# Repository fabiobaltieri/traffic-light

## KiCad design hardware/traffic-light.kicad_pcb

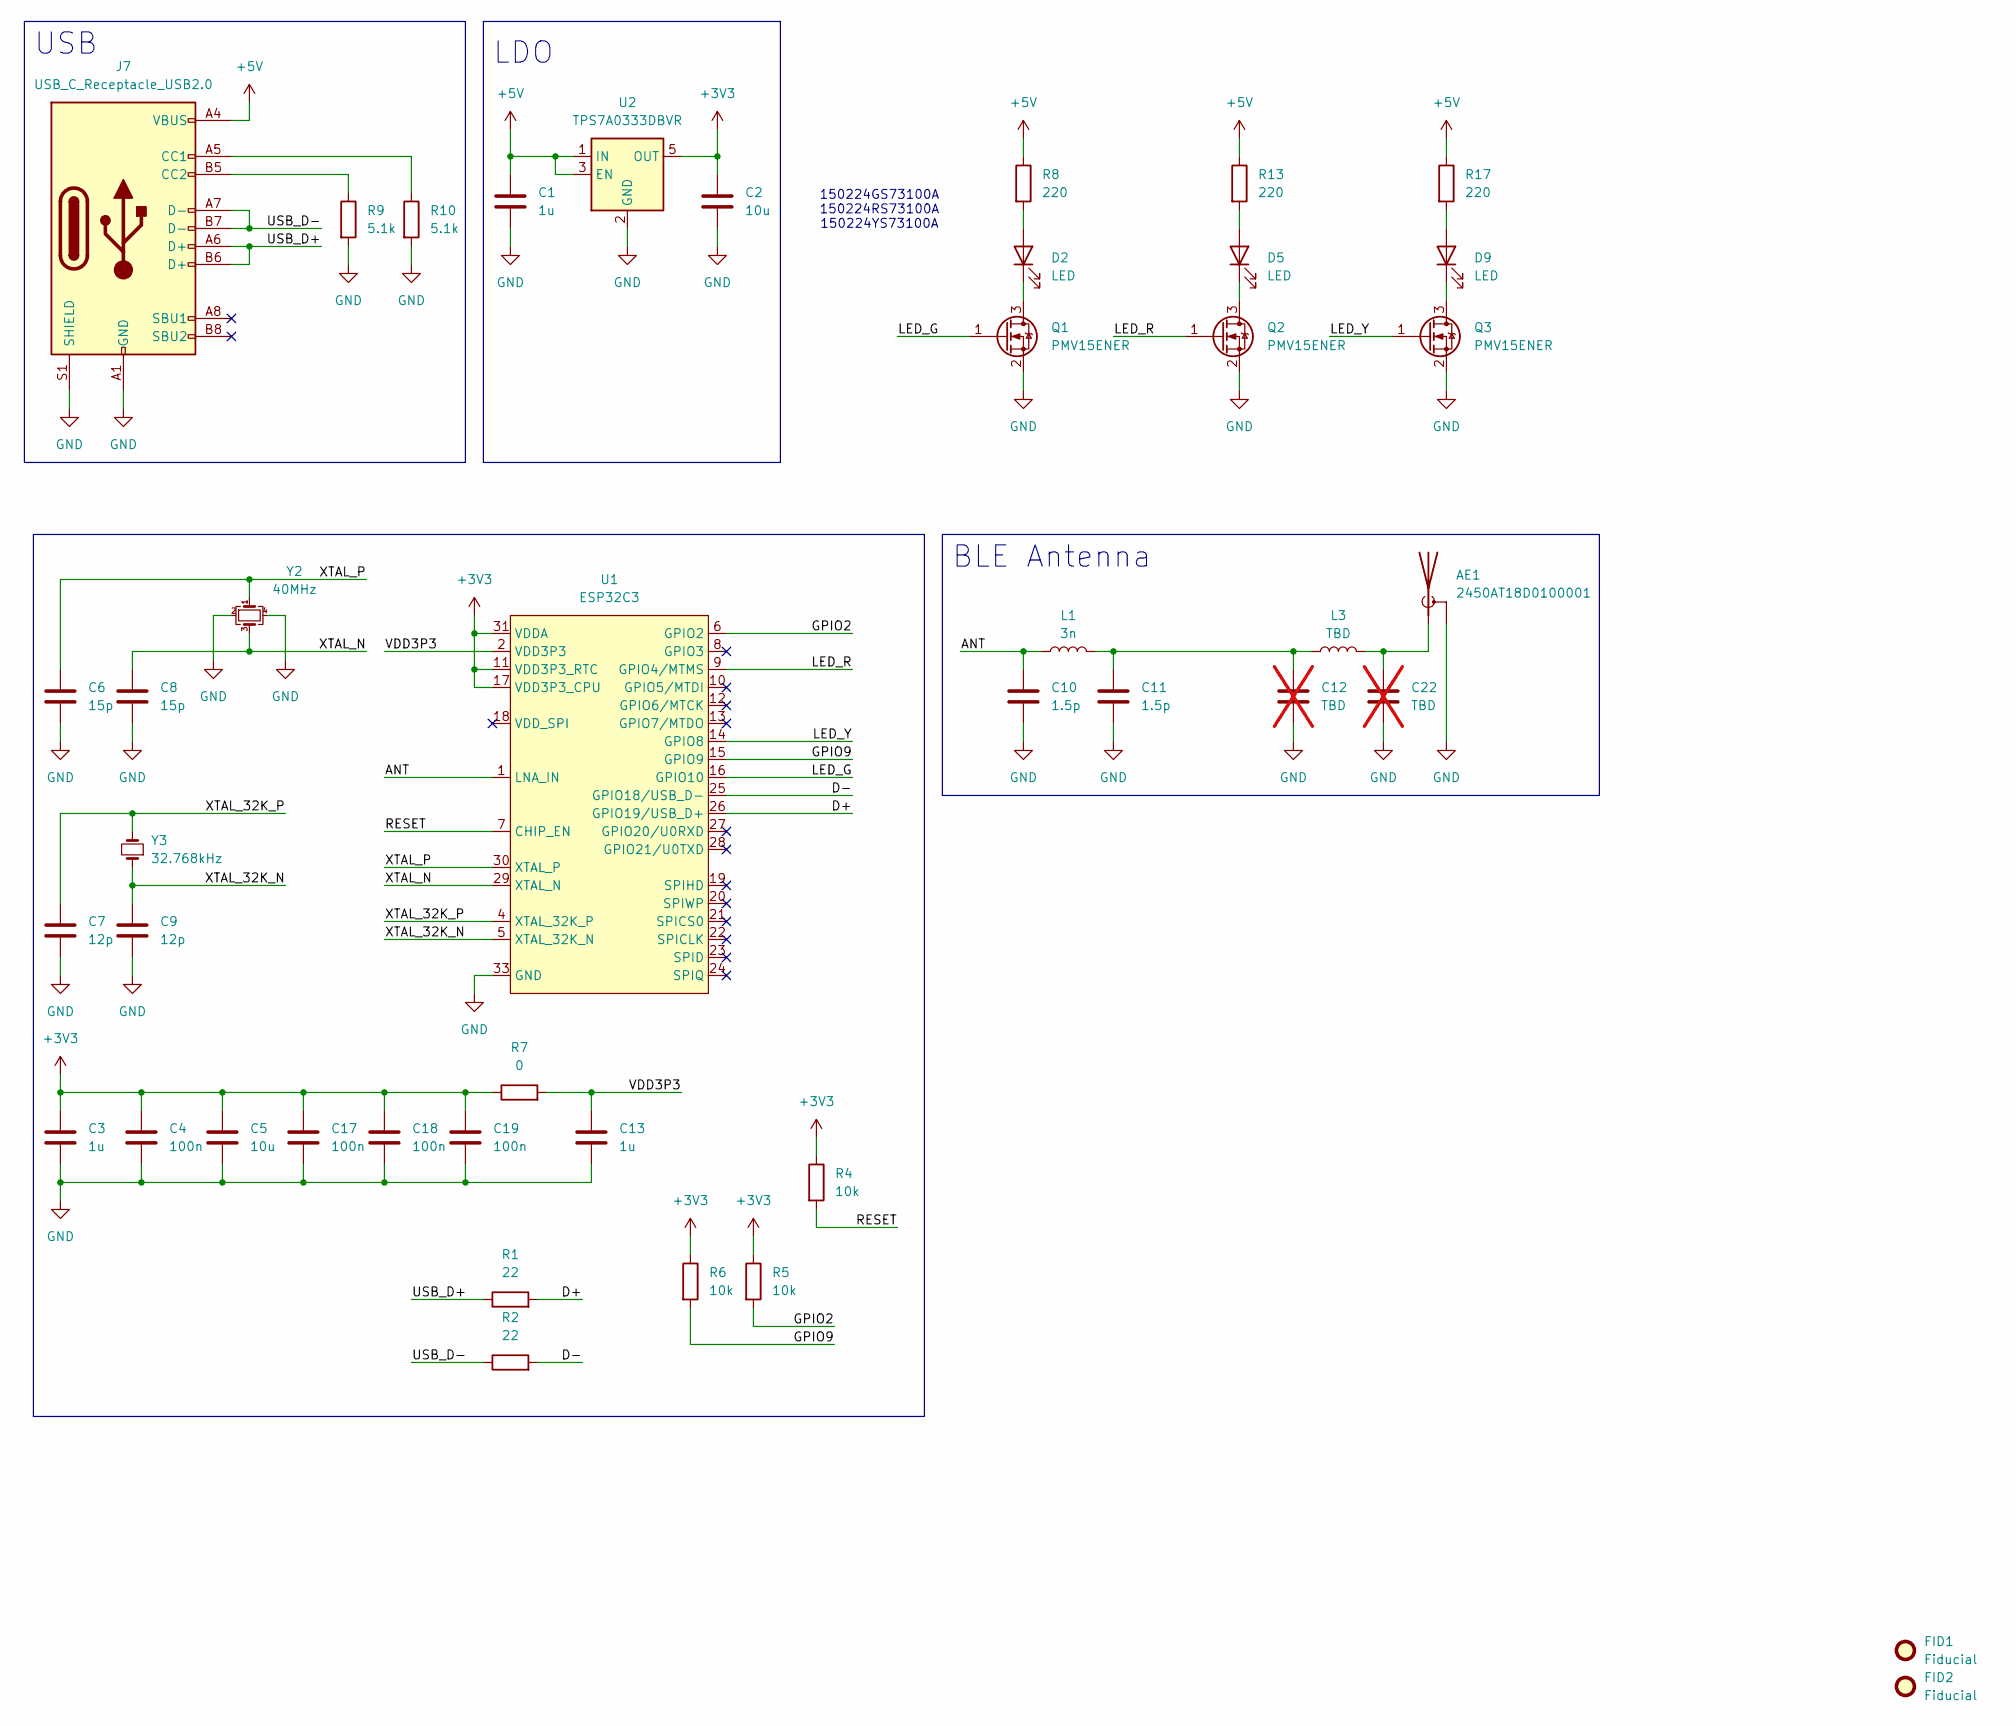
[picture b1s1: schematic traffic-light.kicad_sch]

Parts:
AE1: 2450AT18D0100001; 2450AT18D0100001-R
C1, C3, C13: 1u; C_0402_Worthington
C2, C5: 10u; C_0402_Worthington
C4, C17, C18, C19: 100n; C_0402_Worthington
C6, C8: 15p; C_0402_Worthington
C7, C9: 12p; C_0402_Worthington
C10, C11: 1.5p; C_0402_Worthington
C12, C22: TBD; C_0402_Worthington; not fitted
D2, D5, D9: LED; Wurth_LED_2214
FID1, FID2: Fiducial; Fiducial_0.75mm_Mask1.5mm
J7: USB_C_Receptacle_USB2.0; USB_C_Receptacle_JAE_DX07S016JA1R1500
L1: 3n; L_0402_Worthington
L3: TBD; L_0402_Worthington
Q1, Q2, Q3: PMV15ENER; SOT-23
R1, R2: 22; R_0603_1608Metric
R4, R5, R6: 10k; R_0402_Worthington
R7: 0; R_0402_Worthington
R8, R13, R17: 220; R_0402_Worthington
R9, R10: 5.1k; R_0402_Worthington
U1: ESP32C3; QFN-32-1EP_5x5mm_P0.5mm_EP3.7x3.7mm
U2: TPS7A0333DBVR; SOT-23-5
Y2: 40MHz; Crystal_SMD_2016-4Pin_2.0x1.6mm
Y3: 32.768kHz; Crystal_SMD_2012-2Pin_2.0x1.2mm

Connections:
+3V3: C2.1, C3.1, C4.1, C5.1, C17.1, C18.1, C19.1, R4.1, R5.1, R6.1, R7.1, U1.11 (VDD3P3_RTC), U1.17 (VDD3P3_CPU), U1.31 (VDDA), U1.32 (VDDA), U2.5 (OUT)
+5V: C1.1, J7.A4 (VBUS), J7.A9 (VBUS), J7.B4 (VBUS), J7.B9 (VBUS), R8.1, R13.1, R17.1, U2.1 (IN), U2.3 (EN)
/ANT: C10.1, L1.1, U1.1 (LNA_IN)
/D+: R1.2, U1.26 (GPIO19/USB_D+)
/D-: R2.2, U1.25 (GPIO18/USB_D-)
/GPIO2: R5.2, U1.6 (GPIO2)
/GPIO9: R6.2, U1.15 (GPIO9)
/LED_G: Q1.1 (G), U1.16 (GPIO10)
/LED_R: Q2.1 (G), U1.9 (GPIO4/MTMS)
/LED_Y: Q3.1 (G), U1.14 (GPIO8)
/RESET: R4.2, U1.7 (CHIP_EN)
/USB_D+: J7.A6 (D+), J7.B6 (D+), R1.1
/USB_D-: J7.A7 (D-), J7.B7 (D-), R2.1
/XTAL_32K_N: C9.1, U1.5 (XTAL_32K_N), Y3.1
/XTAL_32K_P: C7.1, U1.4 (XTAL_32K_P), Y3.2
/XTAL_N: C8.1, U1.29 (XTAL_N), Y2.3
/XTAL_P: C6.1, U1.30 (XTAL_P), Y2.1
GND: AE1.2 (Shield), C1.2, C2.2, C3.2, C4.2, C5.2, C6.2, C7.2, C8.2, C9.2, C10.2, C11.2, C12.2, C13.2, C17.2, C18.2, C19.2, C22.2, J7.A1 (GND), J7.A12 (GND), J7.B1 (GND), J7.B12 (GND), J7.S1 (SHIELD), Q1.2 (S), Q2.2 (S), Q3.2 (S), R9.2, R10.2, U1.33 (GND), U2.2 (GND), Y2.2, Y2.4
unnamed: AE1.1 (A), C22.1, L3.1
unnamed: C11.1, C12.1, L1.2, L3.2
unnamed: D2.2 (A), R8.2
unnamed: D2.1 (K), Q1.3 (D)
unnamed: D5.2 (A), R13.2
unnamed: D5.1 (K), Q2.3 (D)
unnamed: D9.2 (A), R17.2
unnamed: D9.1 (K), Q3.3 (D)
unnamed: J7.A5 (CC1), R10.1
unnamed: J7.B5 (CC2), R9.1
VDD3P3: C13.1, R7.2, U1.2 (VDD3P3), U1.3 (VDD3P3)

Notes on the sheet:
USB
150224GS73100A 150224RS73100A 150224YS73100A
BLE Antenna
LDO

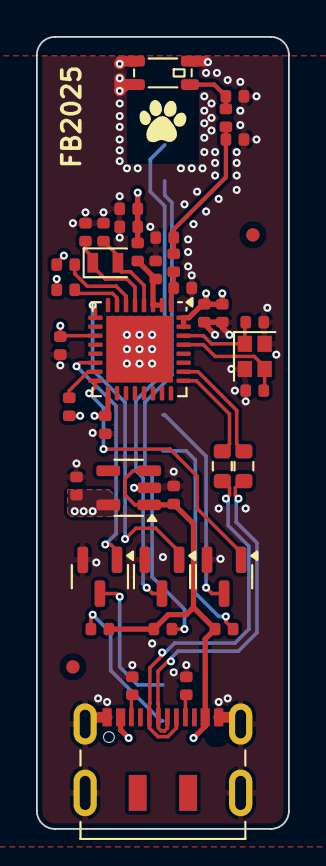
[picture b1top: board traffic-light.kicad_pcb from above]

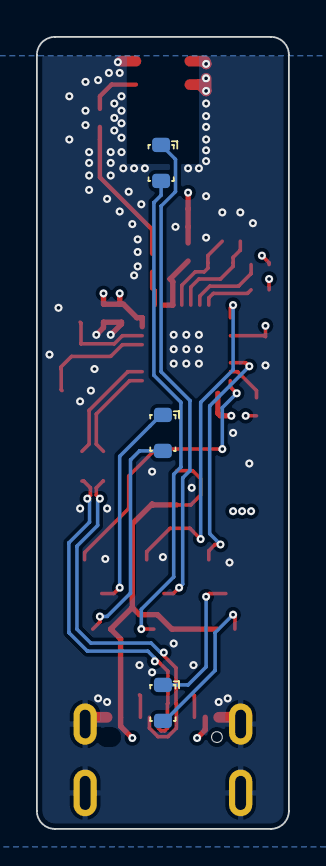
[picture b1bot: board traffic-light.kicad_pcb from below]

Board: 4 copper layers, 14.0 x 44.0 mm, 44 parts (3 on the bottom side), 29 nets.

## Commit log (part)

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2025-08-24 initial import
2025-09-02 fw: fix a horrible typo
2025-09-02 add build.yml
2025-09-02 build: add -a to west blobs fetch
2025-09-03 build: add blobs caching
2025-11-18 fw: posix api update
2026-01-07 fw: set board full_name
2026-01-28 fw: tls api update
2026-03-21 fw: api update
2026-05-09 fw: update few kconfig options
2026-05-12 west.yml: add hostapd
